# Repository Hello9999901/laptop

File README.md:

# anyon e

*also stylized as anyon_e*

A highly integrated, high end, open source laptop.

Mission: to disprove the idea that technology is either repairable and open or integrated and closed.

#

#### Features:

- RK3588 SoC Motherboard
  - CM3588-based
  - USB-C USB3.1 Gen 1
  - ESP32-S3 embedded controller
- Powertrain
  - ESP32-S3 embedded controller
  - ~60Wh Li-ion battery pack
- Peripherals
  - Wireless mechanical keyboard
  - Glass-topped multi-touch trackpad
- 4K AMOLED 13.3" display
- Anodized aluminum CNC chassis

#

#### YouTube Video:

#

*[ **an**-yon ]*

*exotic particles whose quantum statistics are neither bosonic nor fermionic.*[^1]

Integrated like bosons, distinct like fermions.

#

Thank you to the Phillips Exeter Academy Science Department for supporting this project.
*Non Sibi. Knowledge and Goodness. Youth From Every Quarter.* [^2]

[^1]: H. Bartolomei et al. ,Fractional statistics in anyon collisions.Science368,173-177(2020).DOI:10.1126/science.aaz5601

[^2]: Byran Huang's ('25) 2024-25 Fall Term Senior Project. Thank you to my advisors, Mr. Brad Robinson and Mr. Charles Mamolo.

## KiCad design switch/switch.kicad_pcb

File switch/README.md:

# Switch

Power switch PCB with LEDs under a translucent PETG button.

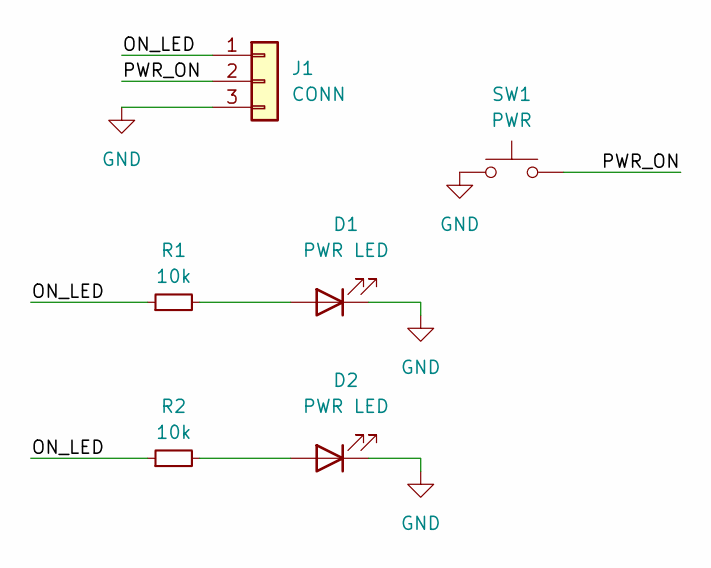
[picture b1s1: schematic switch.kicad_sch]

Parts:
D1, D2: PWR LED; LED_0603_1608Metric
J1: CONN; PinHeader_1x03_P1.27mm_Vertical
R1, R2: 10k; R_0402_1005Metric
SW1: PWR; SW_Push_1P1T_XKB_TS-1187A

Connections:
/ON_LED: J1.1, R1.1, R2.1
/PWR_ON: J1.2, SW1.2
GND: D1.1 (K), D2.1 (K), J1.3, SW1.1
unnamed: D1.2 (A), R1.2
unnamed: D2.2 (A), R2.2

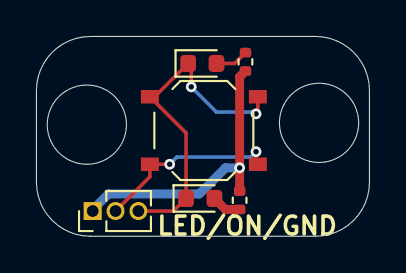
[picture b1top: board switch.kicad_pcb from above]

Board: 2 copper layers, 18.5 x 11.1 mm, 6 parts (0 on the bottom side), 5 nets.

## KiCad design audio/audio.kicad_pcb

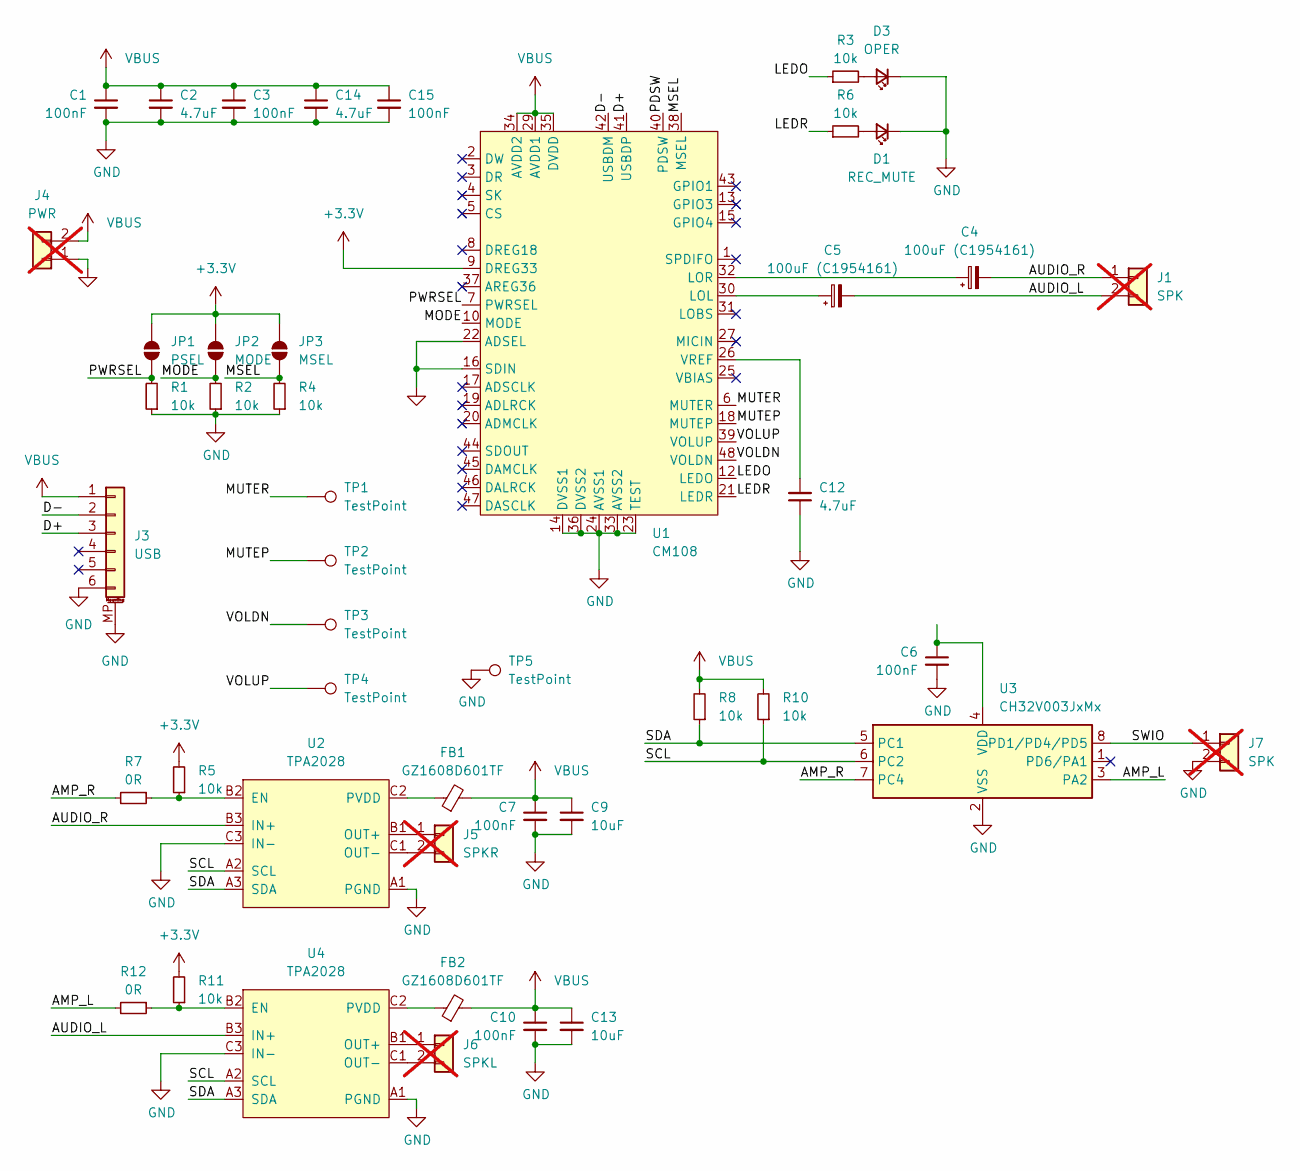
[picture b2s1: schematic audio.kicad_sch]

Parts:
C1, C3, C6, C7, C10, C15: 100nF; C_0603_1608Metric
C2, C12, C14: 4.7uF; C_0603_1608Metric
C4, C5: 100uF (C1954161); C_1206_3216Metric
C9, C13: 10uF; C_0603_1608Metric
D1: REC_MUTE; LED_0603_1608Metric
D3: OPER; LED_0603_1608Metric
FB1, FB2: GZ1608D601TF; L_0603_1608Metric
J1, J7: SPK; PinHeader_1x02_P2.54mm_Vertical; not fitted
J3: USB; FPC-SMD_6P-P0.50_XUNPU_FPC-05F-6PH20; LCSC C2856796
J4: PWR; PinHeader_1x02_P2.54mm_Vertical; not fitted
J5: SPKR; PinHeader_1x02_P2.54mm_Vertical; not fitted
J6: SPKL; PinHeader_1x02_P2.54mm_Vertical; not fitted
JP1: PSEL; SolderJumper-2_P1.3mm_Open_TrianglePad1.0x1.5mm
JP2: MODE; SolderJumper-2_P1.3mm_Open_TrianglePad1.0x1.5mm
JP3: MSEL; SolderJumper-2_P1.3mm_Open_TrianglePad1.0x1.5mm
R1, R2, R3, R4, R5, R6, R8, R10, R11: 10k; R_0603_1608Metric
R7, R12: 0R; R_0603_1608Metric
TP1, TP2, TP3, TP4, TP5: TestPoint; TestPoint_THTPad_1.0x1.0mm_Drill0.5mm
U1: CM108; LQFP-48_7x7mm_P0.5mm
U2, U4: TPA2028
U3: CH32V003JxMx; SOP-8_3.9x4.9mm_P1.27mm

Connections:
+3.3V: JP1.2 (B), JP2.2 (B), JP3.2 (B), R5.2, R11.2, U1.9 (DREG33)
/AMP_L: R12.2, U3.3 (PA2)
/AMP_R: R7.2, U3.7 (PC4)
/AUDIO_L: C5.2, J1.2, U4.B3 (IN+)
/AUDIO_R: C4.2, J1.1, U2.B3 (IN+)
/D+: J3.3, U1.41 (USBDP)
/D-: J3.2, U1.42 (USBDM)
/LEDO: R3.1, U1.12 (LEDO)
/LEDR: R6.1, U1.21 (LEDR)
/MODE: JP2.1 (A), R2.2, U1.10 (MODE)
/MSEL: JP3.1 (A), R4.2, U1.38 (MSEL)
/MUTEP: TP2.1, U1.18 (MUTEP)
/MUTER: TP1.1, U1.6 (MUTER)
/PDSW: U1.40 (PDSW)
/PWRSEL: JP1.1 (A), R1.2, U1.7 (PWRSEL)
/SCL: R10.1, U2.A2 (SCL), U3.6 (PC2), U4.A2 (SCL)
/SDA: R8.1, U2.A3 (SDA), U3.5 (PC1), U4.A3 (SDA)
/SWIO: J7.1, U3.8 (PD1/PD4/PD5)
/VOLDN: TP3.1, U1.48 (VOLDN)
/VOLUP: TP4.1, U1.39 (VOLUP)
GND: C1.2, C2.2, C3.2, C6.2, C7.2, C9.2, C10.2, C12.1, C13.2, C14.2, C15.2, D1.1 (K), D3.1 (K), J3.6, J3.MP (MountPin), J4.1, J7.2, R1.1, R2.1, R4.1, TP5.1, U1.14 (DVSS1), U1.16 (SDIN), U1.22 (ADSEL), U1.23 (TEST), U1.24 (AVSS1), U1.33 (AVSS2), U1.36 (DVSS2), U2.A1 (PGND), U2.C3 (IN-), U3.2 (VSS), U4.A1 (PGND), U4.C3 (IN-)
unnamed: D1.2 (A), R6.2
unnamed: D3.2 (A), R3.2
unnamed: J5.1, U2.B1 (OUT+)
unnamed: J5.2, U2.C1 (OUT-)
unnamed: J6.1, U4.B1 (OUT+)
unnamed: J6.2, U4.C1 (OUT-)
unnamed: C5.1, U1.30 (LOL)
unnamed: C4.1, U1.32 (LOR)
unnamed: C12.2, U1.26 (VREF)
unnamed: R5.1, R7.1, U2.B2 (EN)
unnamed: FB1.1, U2.C2 (PVDD)
unnamed: C6.1, U3.4 (VDD)
unnamed: R11.1, R12.1, U4.B2 (EN)
unnamed: FB2.1, U4.C2 (PVDD)
VBUS: C1.1, C2.1, C3.1, C7.1, C9.1, C10.1, C13.1, C14.1, C15.1, FB1.2, FB2.2, J3.1, J4.2, R8.2, R10.2, U1.29 (AVDD1), U1.34 (AVDD2), U1.35 (DVDD)

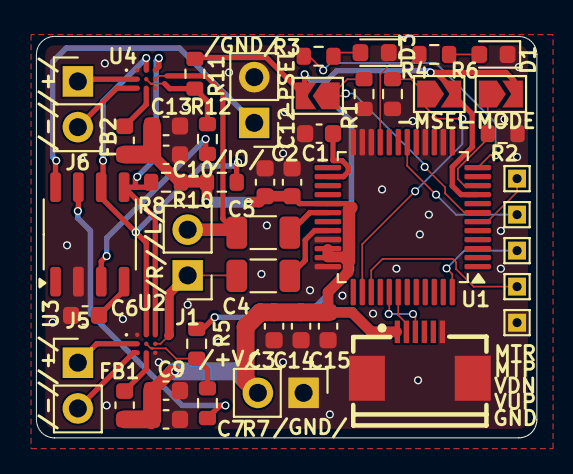
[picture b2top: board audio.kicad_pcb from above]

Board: 2 copper layers, 27.8 x 22.3 mm, 46 parts (0 on the bottom side), 35 nets.

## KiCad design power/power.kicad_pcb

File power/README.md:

# Power

Separate power system because integration is high risk.

NOTE:

The powertrain's VBUS/VBAT system needs to be swapped. Please read schematic for futher detail!

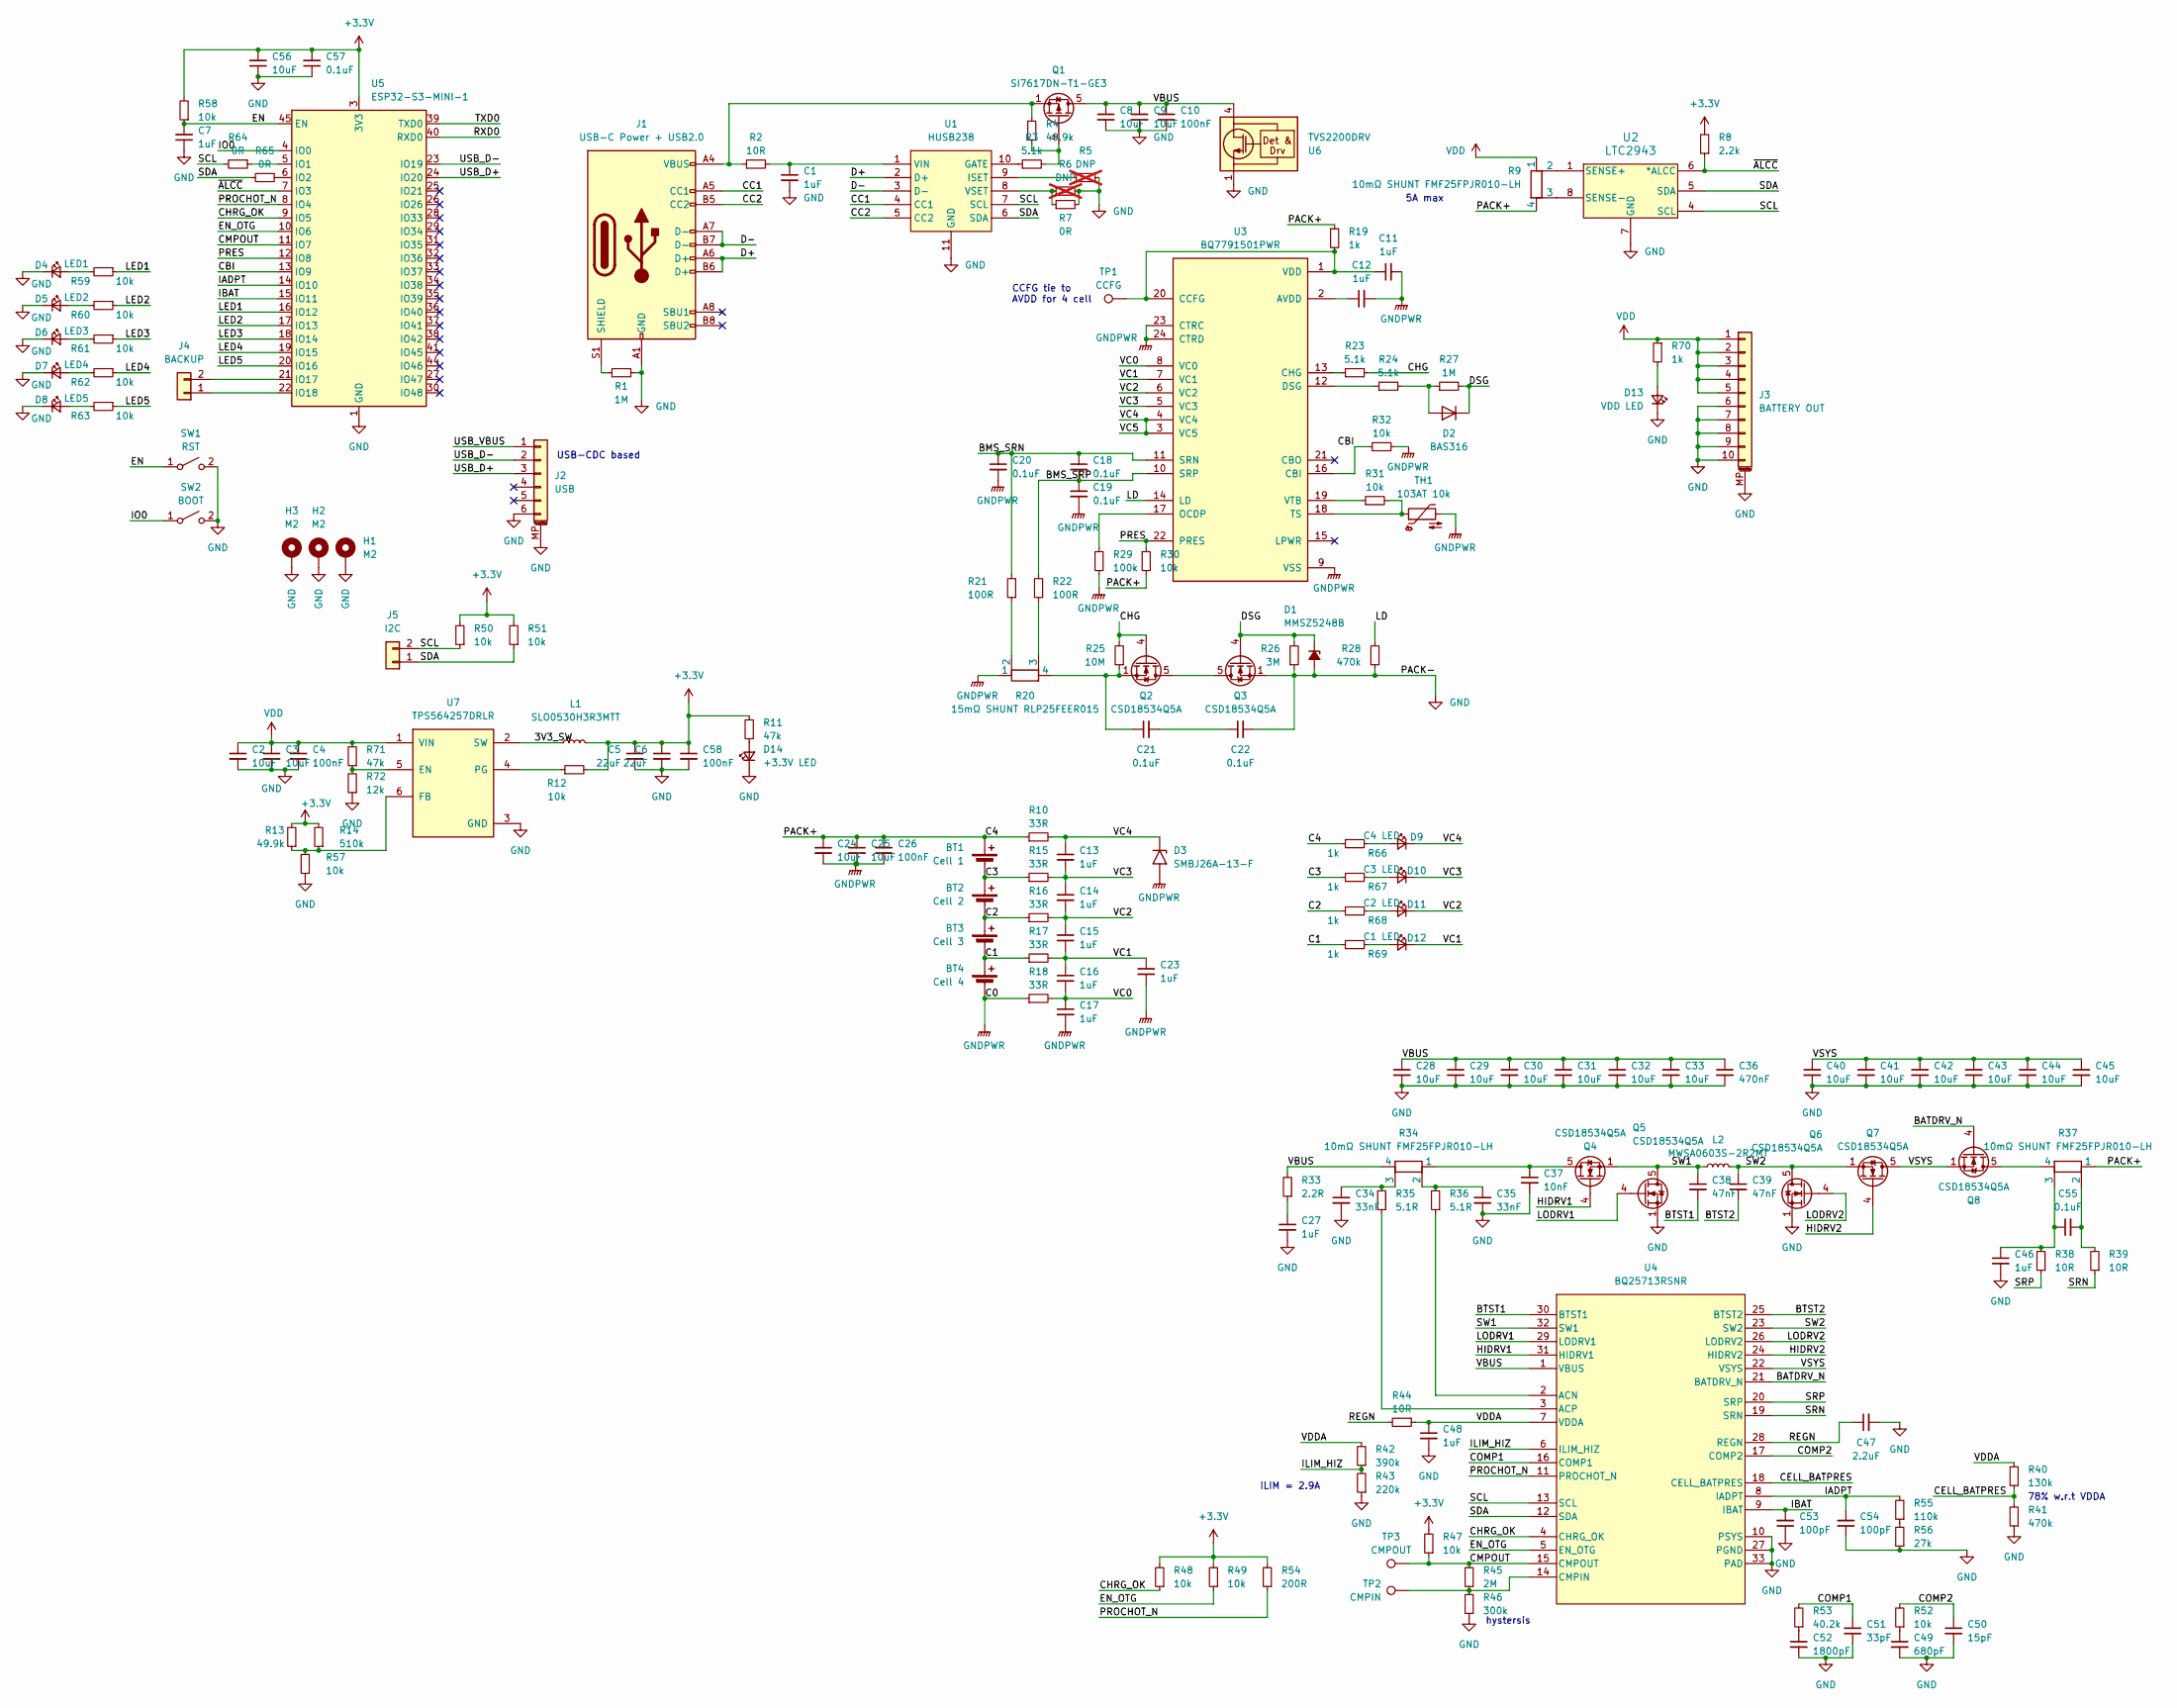
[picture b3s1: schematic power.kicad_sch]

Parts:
BT1: Cell 1; PinHeader_1x02_P2.54mm_Vertical
BT2: Cell 2; PinHeader_1x02_P2.54mm_Vertical
BT3: Cell 3; PinHeader_1x02_P2.54mm_Vertical
BT4: Cell 4; PinHeader_1x02_P2.54mm_Vertical
C1, C7: 1uF; C_0603_1608Metric; LCSC C15849
C2, C3, C8, C9, C24, C25, C28, C29, C30, C31, C32, C33, C40, C41, C42, C43, C44, C45, C56: 10uF; C_0603_1608Metric; LCSC C913517
C4, C58: 100nF; C_0402_1005Metric; LCSC C307331
C5, C6: 22uF; C_0603_1608Metric; LCSC C162690
C10, C26: 100nF; C_0603_1608Metric; LCSC C307331
C11, C12, C13, C14, C15, C16, C17, C23, C27, C46, C48: 1uF; C_0603_1608Metric; LCSC C913517
C18, C19, C20, C21, C22, C55: 0.1uF; C_0603_1608Metric; LCSC C913517
C34, C35: 33nF; C_0603_1608Metric; LCSC C913517
C36: 470nF; C_0603_1608Metric; LCSC C913517
C37: 10nF; C_0603_1608Metric; LCSC C913517
C38, C39: 47nF; C_0603_1608Metric; LCSC C913517
C47: 2.2uF; C_0603_1608Metric; LCSC C913517
C49: 680pF; C_0603_1608Metric; LCSC C913517
C50: 15pF; C_0603_1608Metric; LCSC C913517
C51: 33pF; C_0603_1608Metric; LCSC C913517
C52: 1800pF; C_0603_1608Metric; LCSC C913517
C53, C54: 100pF; C_0603_1608Metric; LCSC C913517
C57: 0.1uF; C_0603_1608Metric; LCSC C14663
D1: MMSZ5248B; D_SOD-123; LCSC C82088
D2: BAS316; D_SOD-323; LCSC C109218
D3: SMBJ26A-13-F; D_SMB; LCSC C135062
D4: LED1; LED_0603_1608Metric; LCSC C2290
D5: LED2; LED_0603_1608Metric; LCSC C2290
D6: LED3; LED_0603_1608Metric; LCSC C2290
D7: LED4; LED_0603_1608Metric; LCSC C2290
D8: LED5; LED_0603_1608Metric; LCSC C2290
D9: C4 LED; LED_0603_1608Metric; LCSC C2286
D10: C3 LED; LED_0603_1608Metric; LCSC C2286
D11: C2 LED; LED_0603_1608Metric; LCSC C2286
D12: C1 LED; LED_0603_1608Metric; LCSC C2286
D13: VDD LED; LED_0603_1608Metric; LCSC C72038
D14: +3.3V LED; LED_0603_1608Metric
H1, H2, H3: M2; MountingHole_2.2mm_M2_Pad_Via
J1: USB-C Power + USB2.0; USB_C_Receptacle_HRO_TYPE-C-31-M-12; LCSC C165948
J2: USB; FPC-SMD_6P-P0.50_XUNPU_FPC-05F-6PH20; LCSC C2856796
J3: BATTERY OUT; Molex_PicoBlade_53048-1010_1x10_P1.25mm_Horizontal; LCSC C564042
J4: BACKUP; PinHeader_1x02_P2.54mm_Vertical
J5: I2C; PinHeader_1x02_P2.54mm_Vertical
L1: SLO0530H3R3MTT; L_Chilisin_BMRA00050530; LCSC C408446
L2: MWSA0603S-2R2MT; L_Sunlord_MWSA0603S; LCSC C408445
Q1: SI7617DN-T1-GE3; Vishay_PowerPAK_1212-8_Single; LCSC C727607
Q2, Q3, Q4, Q5, Q6, Q7, Q8: CSD18534Q5A; TDSON-8-1; LCSC C115943
R1, R27: 1M; R_0603_1608Metric; LCSC C22935
R2: 10R; R_0603_1608Metric; LCSC C22859
R3, R23, R24: 5.1k; R_0603_1608Metric; LCSC C23186
R4: 49.9k; R_0603_1608Metric; LCSC C23184
R5, R6: DNP; R_0603_1608Metric; not fitted
R7: 0R; R_0603_1608Metric; LCSC C21189
R8: 2.2k; R_0603_1608Metric; LCSC C4190
R9, R34, R37: 10mΩ SHUNT FMF25FPJR010-LH; R_Shunt_Vishay_WSK2512_6332Metric_T1.19mm; LCSC C105366
R10, R15, R16, R17, R18: 33R; R_0603_1608Metric; LCSC C23140
R11: 47k; R_0402_1005Metric; LCSC C25744
R12, R57: 10k; R_0402_1005Metric; LCSC C25744
R13: 49.9k; R_0402_1005Metric; LCSC C25897
R14: 510k; R_0402_1005Metric; LCSC C11616
R19: 1k; R_0603_1608Metric; LCSC C21190
R20: 15mΩ SHUNT RLP25FEER015; R_Shunt_Vishay_WSK2512_6332Metric_T1.19mm; LCSC C393085
R21, R22: 100R; R_0603_1608Metric; LCSC C22775
R25: 10M; R_0603_1608Metric; LCSC C7250
R26: 3M; R_0603_1608Metric; LCSC C23156
R28: 470k; R_0603_1608Metric; LCSC C23178
R29: 100k; R_0603_1608Metric; LCSC C25803
R30, R31, R32: 10k; R_0603_1608Metric; LCSC C25804
R33: 2.2R; R_0603_1608Metric; LCSC C25744
R35, R36: 5.1R; R_0603_1608Metric; LCSC C25744
R38, R39, R44: 10R; R_0603_1608Metric; LCSC C25744
R40: 130k; R_0603_1608Metric; LCSC C25744
R41: 470k; R_0603_1608Metric; LCSC C25744
R42: 390k; R_0603_1608Metric; LCSC C25744
R43: 220k; R_0603_1608Metric; LCSC C25744
R45: 2M; R_0603_1608Metric; LCSC C25744
R46: 300k; R_0603_1608Metric; LCSC C25744
R47, R48, R49, R50, R51, R52, R58, R59, R60, R61, R62, R63: 10k; R_0603_1608Metric; LCSC C25744
R53: 40.2k; R_0603_1608Metric; LCSC C25744
R54: 200R; R_0603_1608Metric; LCSC C25744
R55: 110k; R_0603_1608Metric; LCSC C25744
R56: 27k; R_0603_1608Metric; LCSC C25744
R64, R65: 0R; R_0603_1608Metric; LCSC C25744
R66, R67, R68, R69, R70: 1k; R_0603_1608Metric; LCSC C25744
R71: 47k; R_0402_1005Metric; LCSC C25897
R72: 12k; R_0402_1005Metric; LCSC C25897
SW1: RST; SW_Push_1P1T_XKB_TS-1187A; LCSC C318884
SW2: BOOT; SW_Push_1P1T_XKB_TS-1187A; LCSC C318884
TH1: 103AT 10k; PinHeader_1x02_P2.54mm_Vertical
TP1: CCFG; TestPoint_Pad_2.0x2.0mm
TP2: CMPIN; TestPoint_Pad_2.0x2.0mm
TP3: CMPOUT; TestPoint_Pad_2.0x2.0mm
U1: HUSB238; DFN-10_L3.0-W3.0-P0.50-BL-EP2.5; LCSC Part C7471904
U2: LTC2943; DFN-8_DD_LIT; LCSC C107797
U3: BQ7791501PWR; SOP65P640X120-24N; PARTREV H; LCSC C2876946
U4: BQ25713RSNR; RSN0032B; LCSC C2878935
U5: ESP32-S3-MINI-1; ESP32-S2-MINI-1; LCSC C3013941
U6: TVS2200DRV; WSON-6-1EP_2x2mm_P0.65mm_EP1x1.6mm; LCSC C523793
U7: TPS564257DRLR; SOT50P160X60-6N; PARTREV A; LCSC C19272233

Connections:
+3.3V: C5.1, C6.1, C56.2, C57.2, C58.1, L1.2, R8.2, R11.2, R12.2, R13.2, R14.2, R47.2, R48.2, R49.2, R50.2, R51.2, R54.2, R58.2, U5.3 (3V3)
/3V3_SW: L1.1, U7.2 (SW)
/BATDRV_N: Q8.4 (G), U4.21 (BATDRV_N)
/BMS_SRN: C18.1, C20.1, R21.2, U3.11 (SRN)
/BMS_SRP: C18.2, C19.1, R22.2, U3.10 (SRP)
/BTST1: C38.2, U4.30 (BTST1)
/BTST2: C39.2, U4.25 (BTST2)
/C1: BT3.2 (-), BT4.1 (+), R17.1, R69.1
/C2: BT2.2 (-), BT3.1 (+), R16.1, R68.1
/C3: BT1.2 (-), BT2.1 (+), R15.1, R67.1
/C4: BT1.1 (+), C24.1, C25.1, C26.1, R9.4, R10.1, R19.1, R30.2, R37.1, R66.1
/CBI: R32.1, U3.16 (CBI), U5.13 (IO9)
/CC1: J1.A5 (CC1), U1.4 (CC1)
/CC2: J1.B5 (CC2), U1.5 (CC2)
/CELL_BATPRES: R40.1, R41.2, U4.18 (CELL_BATPRES)
/CHG: Q2.4 (G), R23.2, R25.2
/CHRG_OK: R48.1, U4.4 (CHRG_OK), U5.9 (IO5)
/CMPOUT: R45.2, R47.1, TP3.1, U4.15 (CMPOUT), U5.11 (IO7)
/COMP1: C51.1, R53.2, U4.16 (COMP1)
/COMP2: C50.1, R52.2, U4.17 (COMP2)
/D+: J1.A6 (D+), J1.B6 (D+), U1.2 (D+)
/D-: J1.A7 (D-), J1.B7 (D-), U1.3 (D-)
/DSG: D1.1 (K), D2.1 (K), Q3.4 (G), R26.2, R27.2
/EN: C7.2, R58.1, SW1.1 (A), U5.45 (EN)
/EN_OTG: R49.1, U4.5 (EN_OTG), U5.10 (IO6)
/HIDRV1: Q4.4 (G), U4.31 (HIDRV1)
/HIDRV2: Q7.4 (G), U4.24 (HIDRV2)
/IADPT: C54.2, R55.2, U4.8 (IADPT), U5.14 (IO10)
/IBAT: C53.2, U4.9 (IBAT), U5.15 (IO11)
/ILIM_HIZ: R42.1, R43.2, U4.6 (ILIM_HIZ)
/IO0: SW2.1 (A), U5.4 (IO0)
/LD: R28.2, U3.14 (LD)
/LED1: R59.1, U5.16 (IO12)
/LED2: R60.1, U5.17 (IO13)
/LED3: R61.1, U5.18 (IO14)
/LED4: R62.1, U5.19 (IO15)
/LED5: R63.1, U5.20 (IO16)
/LODRV1: Q5.4 (G), U4.29 (LODRV1)
/LODRV2: Q6.4 (G), U4.26 (LODRV2)
/PRES: R30.1, U3.22 (PRES), U5.12 (IO8)
/PROCHOT_N: R54.1, U4.11 (PROCHOT_N), U5.8 (IO4)
/REGN: C47.1, R44.2, U4.28 (REGN)
/RXD0: U5.40 (RXD0)
/SCL: J5.2, R50.1, R64.2, U1.7 (SCL), U2.4 (SCL), U4.13 (SCL)
/SDA: J5.1, R51.1, R65.2, U1.6 (SDA), U2.5 (SDA), U4.12 (SDA)
/SRN: R39.1, U4.19 (SRN)
/SRP: R38.1, U4.20 (SRP)
/SW1: C38.1, L2.1, Q4.1 (S), Q4.2 (S), Q4.3 (S), Q5.5 (D), U4.32 (SW1)
/SW2: C39.1, L2.2, Q6.5 (D), Q7.1 (S), Q7.2 (S), Q7.3 (S), U4.23 (SW2)
/TXD0: U5.39 (TXD0)
/USB_D+: J2.3, U5.24 (IO20)
/USB_D-: J2.2, U5.23 (IO19)
/USB_VBUS: J2.1
/VBUS: C8.1, C9.1, C10.1, C28.1, C29.1, C30.1, C31.1, C32.1, C33.1, C36.1, Q1.5 (D), R33.2, R34.4, U4.1 (VBUS), U6.4 (IN), U6.5 (IN), U6.6 (IN)
/VC0: C16.2, C17.1, R18.2, U3.8 (VC0)
/VC1: C15.2, C16.1, C23.1, D12.1 (K), R17.2, U3.7 (VC1)
/VC2: C14.2, C15.1, D11.1 (K), R16.2, U3.6 (VC2)
/VC3: C13.2, C14.1, D10.1 (K), R15.2, U3.5 (VC3)
/VC4: C13.1, D3.1 (A1), D9.1 (K), R10.2, U3.3 (VC5), U3.4 (VC4)
/VDDA: C48.1, R40.2, R42.2, R44.1, U4.7 (VDDA)
/VSYS: C40.1, C41.1, C42.1, C43.1, C44.1, C45.1, Q7.5 (D), Q8.1 (S), Q8.2 (S), Q8.3 (S), U4.22 (VSYS)
/~ALCC: R8.1, U2.6 (*ALCC), U5.7 (IO3)
GND: C1.2, C2.2, C3.2, C4.2, C5.2, C6.2, C7.1, C8.2, C9.2, C10.2, C22.2, C27.2, C28.2, C29.2, C30.2, C31.2, C32.2, C33.2, C34.2, C35.2, C36.2, C37.2, C40.2, C41.2, C42.2, C43.2, C44.2, C45.2, C46.2, C47.2, C48.2, C49.2, C50.2, C51.2, C52.2, C53.1, C54.1, C56.1, C57.1, C58.2, D1.2 (A), D4.1 (K), D5.1 (K), D6.1 (K), D7.1 (K), D8.1 (K), D13.1 (K), D14.1 (K), H1.1, H2.1, H3.1, J1.A1 (GND), J1.A12 (GND), J1.B1 (GND), J1.B12 (GND), J2.6, J2.MP (MountPin), J3.6, J3.7, J3.8, J3.9, J3.10, J3.MP (MountPin), Q3.1 (S), Q3.2 (S), Q3.3 (S), Q5.1 (S), Q5.2 (S), Q5.3 (S), Q6.1 (S), Q6.2 (S), Q6.3 (S), R1.2, R5.2, R6.2, R7.2, R26.1, R28.1, R41.1, R43.1, R46.1, R56.1, R57.1, R72.1, SW1.2 (B), SW2.2 (B), U1.11 (GND), U2.2 (GND), U2.3 (GND), U2.7 (GND), U2.9 (EPAD), U4.10 (PSYS), U4.27 (PGND), U4.33 (PAD), U5.1 (GND), U5.2 (GND), U5.42 (GND), U5.43 (GND), U5.46 (GND), U5.47 (GND), U5.48 (GND), U5.49 (GND), U5.50 (GND), U5.51 (GND), U5.52 (GND), U5.53 (GND), U5.54 (GND), U5.55 (GND), U5.56 (GND), U5.57 (GND), U5.58 (GND), U5.59 (GND), U5.60 (GND), U5.61 (GND), U5.62 (GND), U5.63 (GND), U5.64 (GND), U5.65 (GND), U6.1 (GND), U6.2 (GND), U6.3 (GND), U6.7 (GND), U7.3 (GND)
GNDPWR: BT4.2 (-), C11.2, C12.2, C17.2, C19.2, C20.2, C23.2, C24.2, C25.2, C26.2, D3.2 (A2), R18.1, R20.1, R29.2, R32.2, TH1.2, U3.9 (VSS), U3.23 (CTRC), U3.24 (CTRD)
unnamed: C21.1, Q2.1 (S), Q2.2 (S), Q2.3 (S), R20.4, R25.1
unnamed: C21.2, C22.1
unnamed: C27.1, R33.1
unnamed: C34.1, R34.3, R35.2
unnamed: C35.1, R34.2, R36.2
unnamed: C46.1, C55.1, R37.3, R38.2
unnamed: C49.1, R52.1
unnamed: C52.1, R53.1
unnamed: C55.2, R37.2, R39.2
unnamed: D2.2 (A), R24.2, R27.1
unnamed: D4.2 (A), R59.2
unnamed: D5.2 (A), R60.2
unnamed: D6.2 (A), R61.2
unnamed: D7.2 (A), R62.2
unnamed: D8.2 (A), R63.2
unnamed: D9.2 (A), R66.2
unnamed: D10.2 (A), R67.2
unnamed: D11.2 (A), R68.2
unnamed: D12.2 (A), R69.2
unnamed: D13.2 (A), R70.2
unnamed: D14.2 (A), R11.1
unnamed: J1.S1 (SHIELD), R1.1
unnamed: J1.A4 (VBUS), J1.A9 (VBUS), J1.B4 (VBUS), J1.B9 (VBUS), Q1.1 (S), Q1.2 (S), Q1.3 (S), R2.1, R4.2
unnamed: J4.1, U5.22 (IO18)
unnamed: J4.2, U5.21 (IO17)
unnamed: Q1.4 (G), R3.2, R4.1
unnamed: Q2.5 (D), Q3.5 (D)
unnamed: C37.1, Q4.5 (D), R34.1
unnamed: Q8.5 (D), R37.4
unnamed: R20.2, R21.1
unnamed: R20.3, R22.1
unnamed: R55.1, R56.2
unnamed: R3.1, U1.10 (GATE)
unnamed: R5.1, U1.9 (ISET)
unnamed: C1.1, R2.2, U1.1 (VIN)
unnamed: R6.1, R7.1, U1.8 (VSET)
unnamed: R9.2, U2.1 (SENSE+)
unnamed: R9.3, U2.8 (SENSE-)
unnamed: C12.1, U3.2 (AVDD)
unnamed: C11.1, R19.2, TP1.1, U3.1 (VDD), U3.20 (CCFG)
unnamed: R23.1, U3.13 (CHG)
unnamed: R24.1, U3.12 (DSG)
unnamed: R29.1, U3.17 (OCDP)
unnamed: R31.2, TH1.1, U3.18 (TS)
unnamed: R31.1, U3.19 (VTB)
unnamed: R36.1, U4.2 (ACN)
unnamed: R35.1, U4.3 (ACP)
unnamed: R45.1, R46.2, TP2.1, U4.14 (CMPIN)
unnamed: R64.1, U5.5 (IO1)
unnamed: R65.1, U5.6 (IO2)
unnamed: R71.1, R72.2, U7.5 (EN)
unnamed: R13.1, R14.1, R57.2, U7.6 (FB)
unnamed: R12.1, U7.4 (PG)
VDD: C2.1, C3.1, C4.1, J3.1, J3.2, J3.3, J3.4, J3.5, R9.1, R70.1, R71.2, U7.1 (VIN)

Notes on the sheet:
hystersis
5A max
ILIM = 2.9A
USB-CDC based
CCFG tie to AVDD for 4 cell
78% w.r.t VDDA

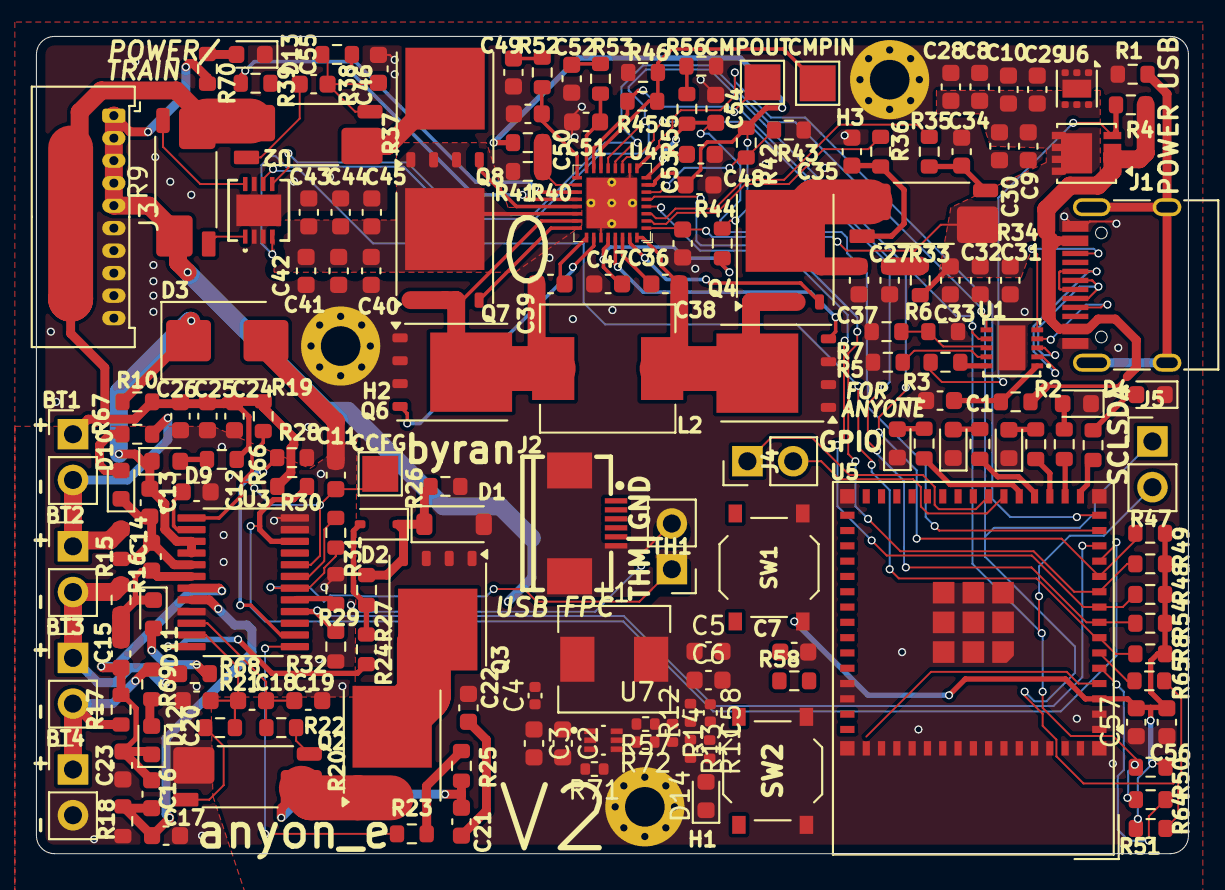
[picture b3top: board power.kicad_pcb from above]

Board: 4 copper layers, 64.0 x 45.4 mm, 179 parts (0 on the bottom side), 115 nets.
